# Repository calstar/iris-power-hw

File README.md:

View this project on [CADLAB.io](https://cadlab.io/project/23273). 

# iris-power-hw

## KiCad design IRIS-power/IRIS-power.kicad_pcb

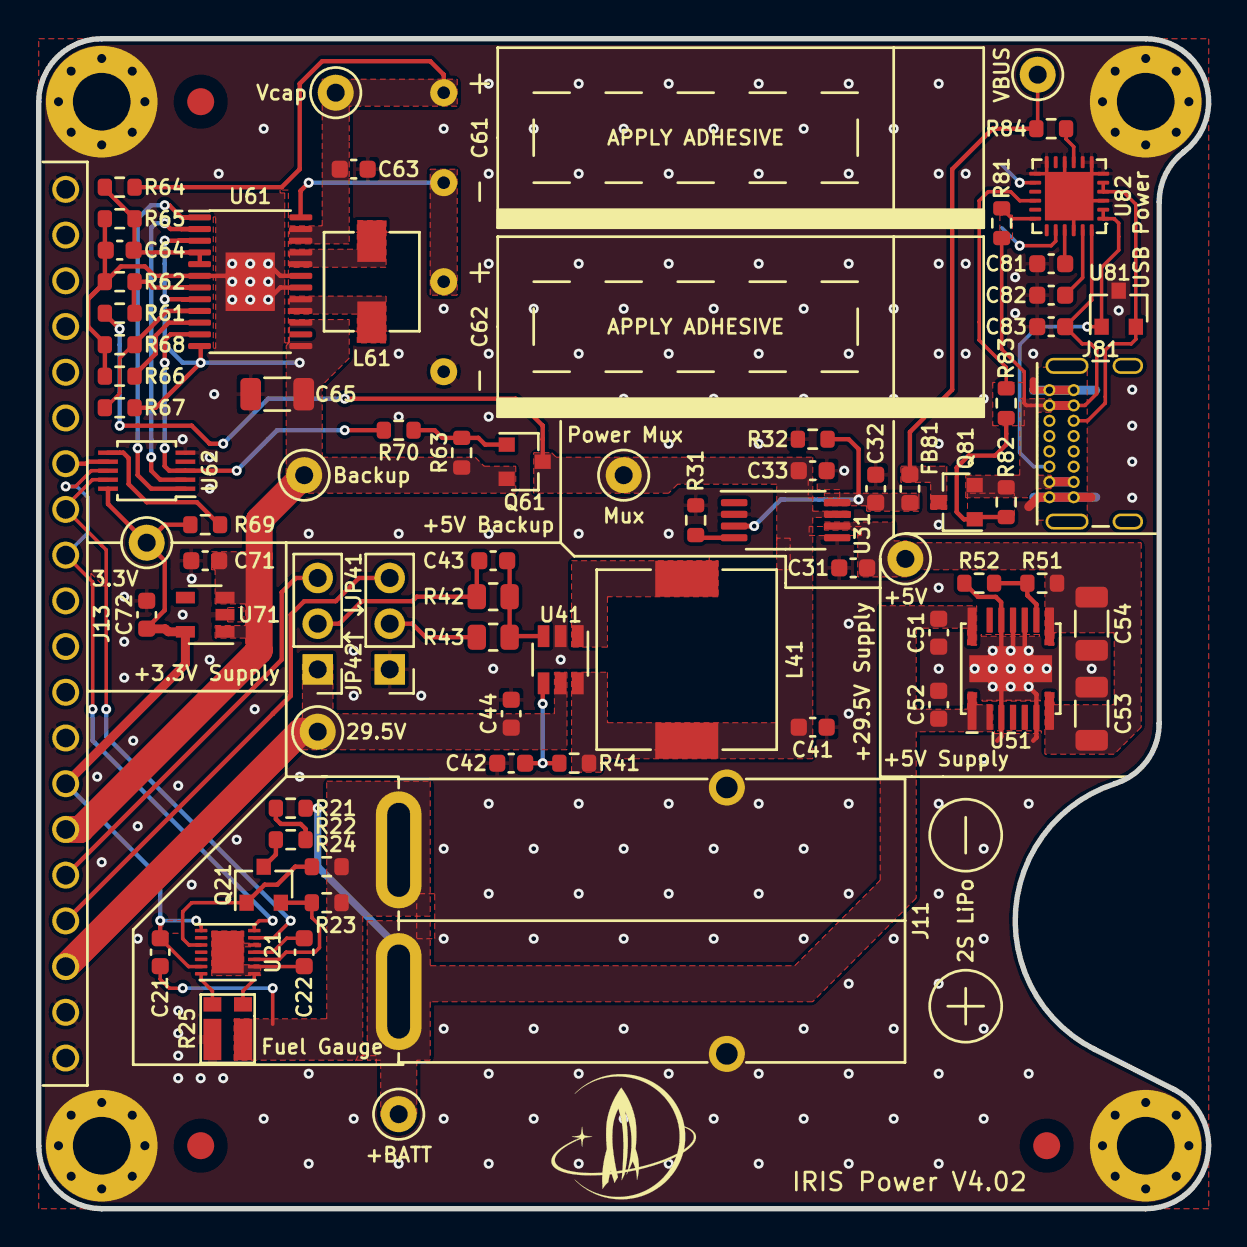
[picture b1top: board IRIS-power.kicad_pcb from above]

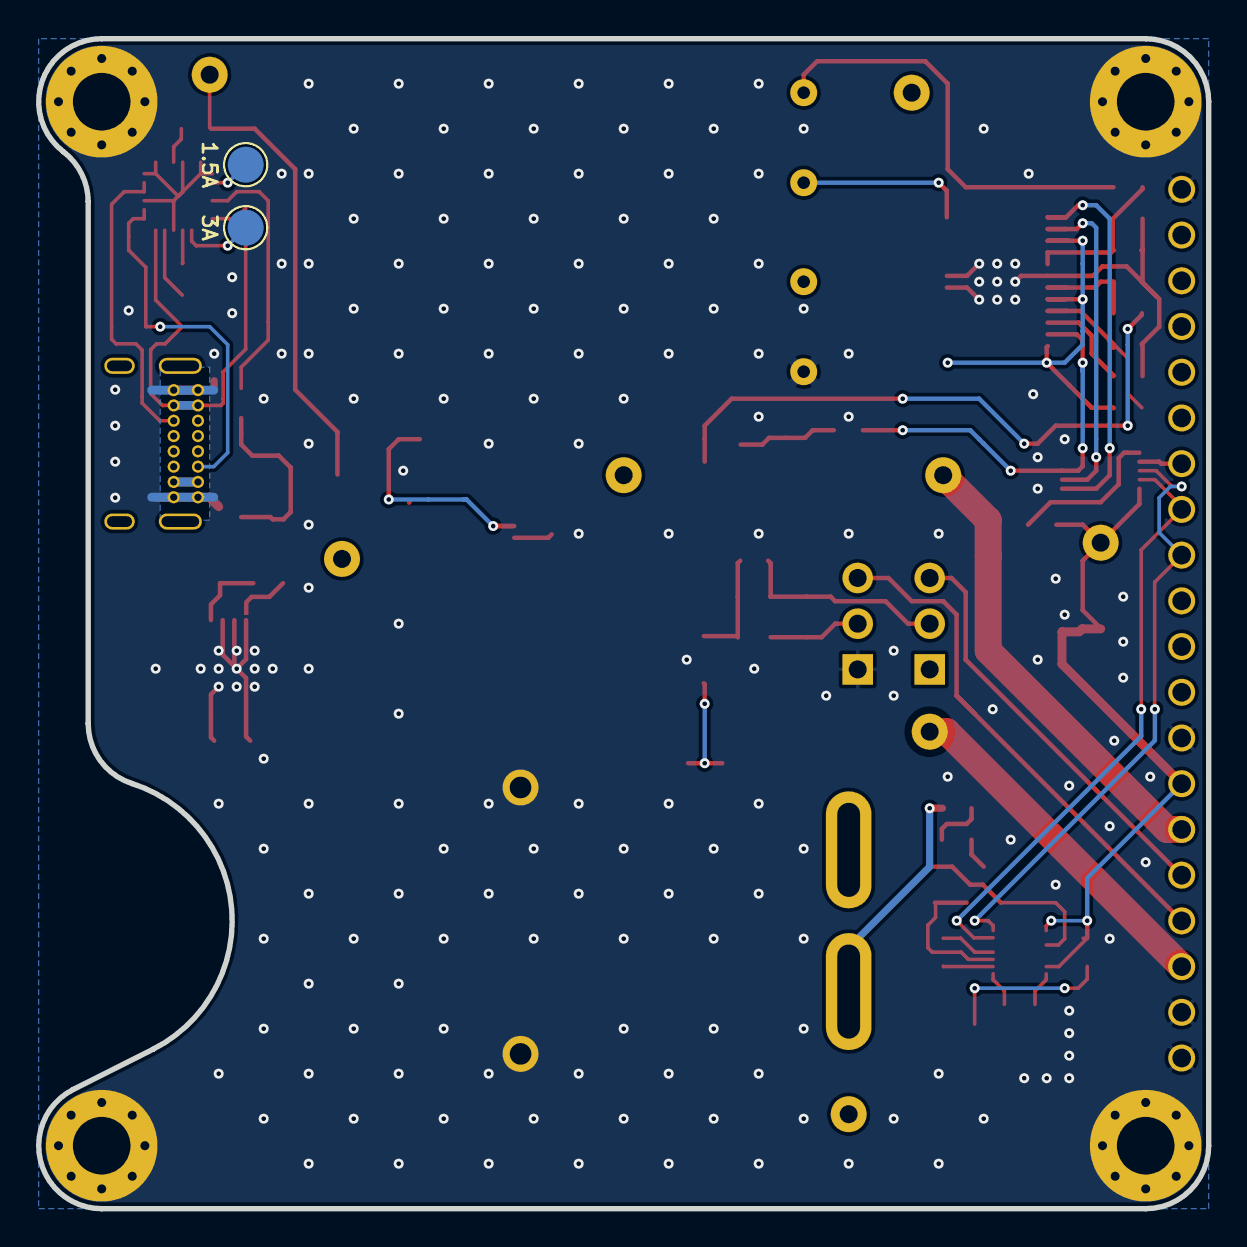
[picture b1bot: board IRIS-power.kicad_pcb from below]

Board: 2 copper layers, 65.0 x 65.0 mm, 84 parts (2 on the bottom side), 55 nets.

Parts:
1.5A, 3A: TestPoint_Probe; TestPoint_Pad_D2.0mm
C21, C31, C32, C64: 0.1uF; C_0603_1608Metric
C22: 0.47uF; C_0603_1608Metric
C33, C51, C52, C63, C72: 10uF; C_0603_1608Metric
C41, C44, C71, C81, C82, C83: 1uF; C_0603_1608Metric
C42: 47nF; C_0603_1608Metric
C43: 22pF; C_0603_1608Metric
C53, C54, C65: 47uF; C_1206_3216Metric
C61, C62: 3.3F; CAP_10x27_5mm_pitch
FB81: Ferrite_Bead; L_0603_1608Metric
FID1, FID2, FID3: Fiducial; Fiducial_1.5mm_Mask3mm
J11: Powerpole; Powerpole_1336G1
J13: Conn_01x20_MountingPin; IRIS_V4_power
J81: USB_C_Receptacle_USB2.0; USB_C_Receptacle_GCT_USB4085_Fixed
JP41, JP42: Jumper_3_Bridged12; PinHeader_1x03_P2.54mm_Vertical
L41: 22uH; 7447714220
L61: 1.5uH; 744316150
NT51, NT61: Net-Tie_2; NetTie-2_SMD_Pad0.5mm
Q21: 2N7002; SOT-23
Q61, Q81: SSM3J328R; SOT-23
R21: 499k; R_0603_1608Metric
R22: 301k; R_0603_1608Metric
R23: 200k; R_0603_1608Metric
R24, R32, R51, R61, R66, R69: 10k; R_0603_1608Metric
R25: 2m; CST0612-FC-R002E
R31: 402R; R_0603_1608Metric
R41: 47k; R_0603_1608Metric
R42: 392k; R_0805_2012Metric
R43: 17.4k; R_0805_2012Metric
R52: 2.49k; R_0603_1608Metric
R62: 3k; R_0603_1608Metric
R63, R82: 100k; R_0603_1608Metric
R64: 3.3M; R_0603_1608Metric
R65: 1M; R_0603_1608Metric
R67: 1.1M; R_0603_1608Metric
R68: 150k; R_0603_1608Metric
R70, R81, R83, R84: 1k; R_0603_1608Metric
TP61: Vcap; TestPoint_Keystone_5000-5004_Miniature
TP101: VBUS; TestPoint_Keystone_5000-5004_Miniature
TP102: +5V; TestPoint_Keystone_5000-5004_Miniature
TP103: +BATT; TestPoint_Keystone_5000-5004_Miniature
TP104: Mux; TestPoint_Keystone_5000-5004_Miniature
TP105: 29.5V; TestPoint_Keystone_5000-5004_Miniature
TP106: Backup; TestPoint_Keystone_5000-5004_Miniature
TP107: 3.3V; TestPoint_Keystone_5000-5004_Miniature
U21: MAX17261
U31: TPS2115APW; TSSOP-8_4.4x3mm_P0.65mm
U41: LT3461A; TSOT-23-6
U51: TPSM53602
U61: LTC3110
U62: PCA9537; TSSOP-10_3x3mm_P0.5mm
U71: TLV75733PDBV; SOT-23-5
U81: TPD2E2U06; SOT-23
U82: STUSB4500LQTR; STUSB4500L

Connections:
/3V Supply/+3.3V: C21.1, C72.1, J13.14, R69.1, TP107.1, U21.1, U21.6, U62.10, U71.5
/3V Supply/VSYS: C65.1, C71.1, J13.15, Q61.2, R63.1, R67.1, TP106.1, U61.3, U61.8, U61.12, U61.13, U61.15, U71.1, U71.3
/5V Backup/+MUX: C33.1, C41.1, L41.1, Q61.3, R41.1, R61.1, TP104.1, U31.7, U41.6
/5V Backup/CAP_OK: U61.1, U62.1
/5V Backup/DIR: R61.2, R62.1, U61.7
/5V Backup/FB: R67.2, R68.1, U61.9
/5V Backup/FBVcap: C64.1, R64.1, R65.2, U61.4, U61.5
/5V Backup/PROG: R66.2, U61.10
/5V Backup/SCL: J13.9, U21.14, U62.8
/5V Backup/SDA: J13.8, U21.13, U62.9
/5V Backup/SW1: L61.1, U61.20, U61.21
/5V Backup/SW2: L61.2, U61.16, U61.17
/5V Backup/Vcap: C61.1, C63.1, R64.2, TP61.1, U61.22, U61.23
/5V Backup/Vmid: C61.2, C62.1, U61.24
/5V Backup/~CHRG: R70.2, U61.11, U62.3
/5V Backup/~CMP_OUT: U61.2, U62.2
/5V Backup/~INT: J13.7, U62.7
/5V Supply/+5V: C31.1, C53.1, C54.1, R51.1, TP102.1, U31.6, U51.7, U51.8
/5V Supply/+BATT: C51.1, C52.1, J11.1, R21.1, TP103.1, U51.1, U51.2, U51.14
/5V Supply/AGND: NT51.2, R52.2
/5V Supply/FB: R51.2, R52.1, U51.9
/Edge Connector/+29.5V: C44.1, J13.18, JP42.1, TP105.1, U41.5
/Edge Connector/FB_HV_N: J13.17, JP41.3
/Edge Connector/FB_HV_P: J13.16, JP42.3
/Fuel Gauge/-BATT: C21.2, J11.2, R23.2, R24.2, R25.1
/Fuel Gauge/CELLX: Q21.2, R23.1, U21.10
/Fuel Gauge/CSN: R25.3, U21.7
/Fuel Gauge/REG: C22.1, U21.11
/Fuel Gauge/SW: Q21.1, R24.1, U21.3
/HV Supply/FB: C43.2, R42.2, R43.1, U41.3
/Power Mux/VUSB: C32.1, FB81.1, R32.1, U31.3, U31.8
/USB Connector/CC1: J81.A5, U81.1, U82.1, U82.2
/USB Connector/CC2: J81.B5, U81.2, U82.4, U82.5
/USB Connector/VBUS: C83.1, J81.A4, J81.A9, J81.B4, J81.B9, Q81.2, R81.1, R82.1, U82.24
GND: C31.2, C32.2, C33.2, C41.2, C42.2, C44.2, C51.2, C52.2, C53.2, C54.2, C62.2, C63.2, C65.2, C71.2, C72.2, C81.2, C82.2, C83.2, J11.MP, J13.1, J13.13, J13.19, J13.20, J13.MP, J81.A1, J81.A12, J81.B1, J81.B12, JP41.1, NT51.1, NT61.2, R25.4, R31.2, R32.2, U31.2, U31.5, U41.2, U51.3, U51.6, U51.10, U51.11, U51.12, U51.15, U61.6, U61.18, U61.19, U61.25, U62.5, U71.2, U81.3, U82.3, U82.6, U82.7, U82.8, U82.10, U82.12, U82.13, U82.22, U82.25
GND1: C22.2, R25.2, U21.8, U21.9, U21.12, U21.15
GNDS: C64.2, NT61.1, R62.2, R65.1, R66.1, R68.2
unnamed: C42.1, R41.2, U41.4
unnamed: C43.1, JP42.2, R42.1
unnamed: C81.1, U82.21
unnamed: C82.1, U82.23
unnamed: FB81.2, Q81.3, R84.1, TP101.1
unnamed: JP41.2, R43.2
unnamed: L41.2, U41.1
unnamed: Q21.3, R22.2
unnamed: Q61.1, R63.2, R70.1
unnamed: Q81.1, R82.2, R83.1
unnamed: R21.2, R22.1
unnamed: R31.1, U31.4
unnamed: R69.2, U62.6
unnamed: R81.2, U82.18
unnamed: R83.2, U82.16
unnamed: R84.2, U82.9
unnamed: 3A.1, U82.20
unnamed: 1.5A.1, U82.14

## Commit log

2020-08-02 Added IRIS power files
2020-08-03 Added new 5V rail, adjusted passives, added fuel gauge
2020-08-03 Added more input protection, revised schematic
2020-08-05 updated library:
2020-08-07 Updated sheets organization
2020-08-07 Updated sheet organization
2020-08-09 Finalized power board V2 schematic, preparing to layout
2020-08-09 Started layout
2020-08-11 Updated layout
2020-08-19 Finished initial layout without gnd plane
2020-08-22 Added some 3D models
2020-08-30 Backlink to CADLAB.io has been added.
2020-08-30 Updated 3D models
2020-10-23 Begin revising for IRIS V4
2020-10-29 Updated IRIS power board for V4
2020-11-06 Improved fuel gauge layout
2020-11-10 Adjusted silkscreen
2020-11-11 USB C power prototype
2020-11-12 Updated HV supply
2020-12-12 Updated to V4.01
2021-01-27 IRIS V4.02
